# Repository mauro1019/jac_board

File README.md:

# jac_board
 Ambulance Light Controller

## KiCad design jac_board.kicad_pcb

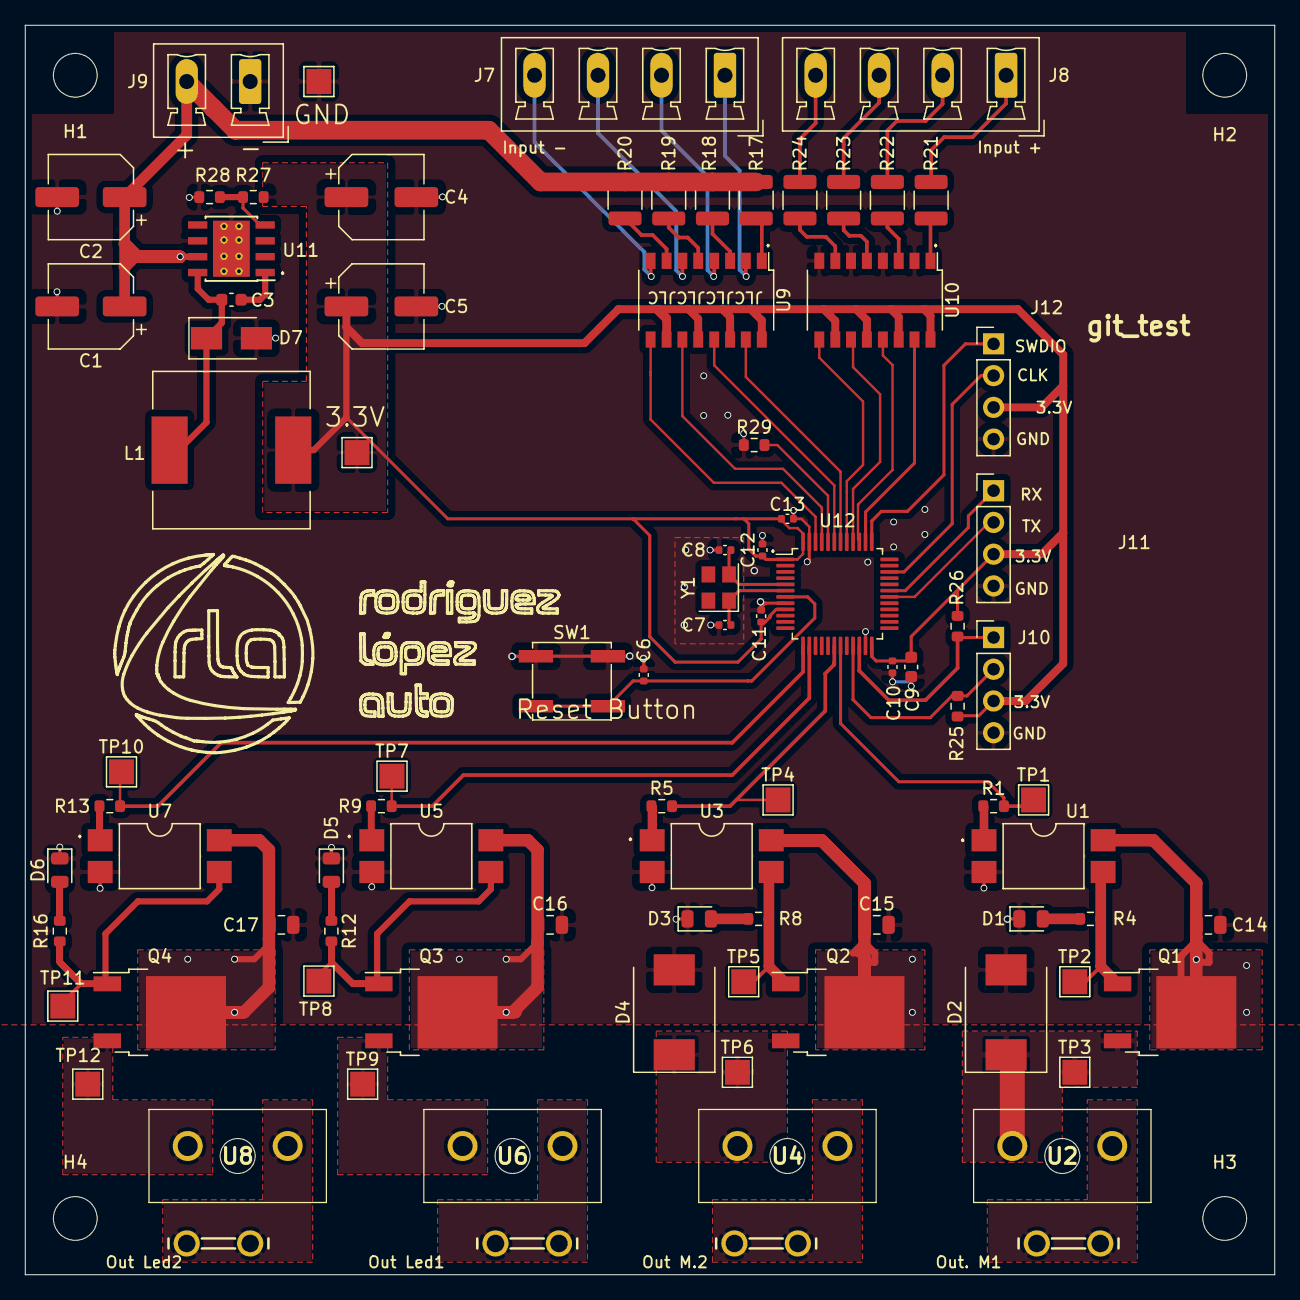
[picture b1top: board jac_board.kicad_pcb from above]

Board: 2 copper layers, 100.0 x 100.0 mm, 92 parts (0 on the bottom side), 64 nets.

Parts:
C1, C2: 22uF; CP_Elec_6.3x7.7
C3: 10nf; C_0603_1608Metric
C4, C5: 150uF; CP_Elec_6.3x5.4
C6, C10, C11, C12, C13: 100nf; C_0402_1005Metric
C7, C8: 16pf; C_0402_1005Metric
C9: 4.7uf; C_0603_1608Metric
C14, C15, C16, C17: 22uf; C_0805_2012Metric
D1, D3, D5, D6: LED; LED_0805_2012Metric
D2, D4: FlyBack Diode; D_SMC
D7: B340; D_SMA
H1, H2, H3, H4: MountingHole; MountingHole_3.5mm
J2, J3, J4, J5: 726386-2
J7, J8: Screw_Terminal_01x04; PhoenixContact_MCV_1,5_4-G-5.08_1x04_P5.08mm_Vertical
J9: Screw_Terminal_01x02; PhoenixContact_MCV_1,5_2-G-5.08_1x02_P5.08mm_Vertical
J10, J11, J12: Conn_01x04_Female; PinHeader_1x04_P2.54mm_Vertical
L1: 22uH; L_12x12mm_H6mm
Q1, Q2, Q3, Q4: KIA50N06BD; TO-252-2
R1, R5, R9, R13: 220; R_0603_1608Metric
R4, R8, R12, R16: 1k; R_0603_1608Metric
R17, R18, R19, R20, R21, R22, R23, R24: 510; R_1210_3225Metric
R25, R26: 4.7k; R_0603_1608Metric
R27, R28: 510; R_0603_1608Metric
R29: 100k; R_0603_1608Metric
SW1: SW_Push; SW_SPST_EVPBF
TP1, TP2, TP3, TP4, TP5, TP6, TP7, TP8, TP9, TP10, TP11, TP12, TP13, TP14: TestPoint; TestPoint_Pad_2.0x2.0mm
U1, U3, U5, U7: LTV-817S; SMDIP-4_W9.53mm
U2, U4, U6, U8: 178.6764.0001; 17867640001
U9, U10: LTV-247; SOP-16_4.4x10.4mm_P1.27mm
U11: TPS5430DDA; TI_SO-PowerPAD-8_ThermalVias
U12: STM32F030C8Tx; LQFP-48_7x7mm_P0.5mm
Y1: 8MHz; Oscillator_SMD_Abracon_ASE-4Pin_3.2x2.5mm

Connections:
+3V3: C4.1, C5.1, C9.1, C10.1, C11.1, C12.1, C13.1, J10.3, J11.3, J12.3, L1.2, R25.2, R26.2, R27.1, TP14.1, U9.10, U9.12, U9.14, U9.16, U10.10, U10.12, U10.14, U10.16, U12.1, U12.9, U12.24, U12.48
+12V: C1.1, C2.1, C14.1, C15.1, C16.1, C17.1, J9.2, Q1.2, Q2.2, Q3.2, Q4.2, R17.2, R18.2, R19.2, R20.2, U1.4, U3.4, U5.4, U7.4, U11.7
/optoMosfet/Sheet60DFA9C4/out_motor: D2.1, Q1.3, TP3.1, U2.1
/optoMosfet/sheet60E0E1BC/out_motor: D4.1, Q2.3, TP6.1, U4.1
GND: C1.2, C2.2, C4.2, C5.2, C6.1, C7.2, C8.2, C9.2, C10.2, C11.2, C12.2, C13.2, C14.2, C15.2, C16.2, C17.2, D1.1, D2.2, D3.1, D4.2, D5.1, D6.1, D7.2, J9.1, J10.4, J11.4, J12.4, R28.2, R29.1, SW1.1, TP13.1, U1.2, U3.2, U5.2, U7.2, U10.2, U10.4, U10.6, U10.8, U11.6, U11.9, U12.8, U12.23, U12.47
unnamed: C3.1, U11.1
unnamed: C3.2, D7.1, L1.1, U11.8
unnamed: D1.2, R4.1
unnamed: D3.2, R8.1
unnamed: D5.2, R12.1
unnamed: D6.2, R16.1
unnamed: J2.1, J2.2, U2.2
unnamed: J3.1, J3.2, U4.2
unnamed: J4.1, J4.2, U6.2
unnamed: J5.1, J5.2, U8.2
unnamed: Q1.1, R4.2, TP2.1, U1.3
unnamed: Q2.1, R8.2, TP5.1, U3.3
unnamed: Q3.1, R12.2, TP8.1, U5.3
unnamed: Q3.3, TP9.1, U6.1
unnamed: Q4.1, R16.2, TP11.1, U7.3
unnamed: Q4.3, TP12.1, U8.1
unnamed: R1.1, U1.1
unnamed: R5.1, U3.1
unnamed: R9.1, U5.1
unnamed: R13.1, U7.1
unnamed: R17.1, U9.1
unnamed: R18.1, U9.3
unnamed: R19.1, U9.5
unnamed: R20.1, U9.7
unnamed: R21.1, U10.1
unnamed: R22.1, U10.3
unnamed: R23.1, U10.5
unnamed: R24.1, U10.7
unnamed: R29.2, U12.44
PA3: R13.2, TP10.1, U12.13
PA4: R9.2, TP7.1, U12.14
PA13: J12.2, U12.34
PA14: J12.1, U12.37
PA15: U10.15, U12.38
PB0: R5.2, TP4.1, U12.18
PB1: R1.2, TP1.1, U12.19
PB3: U10.13, U12.39
PB4: U10.11, U12.40
PB5: U10.9, U12.41
PB6: U9.15, U12.42
PB7: U9.13, U12.43
PB8: U9.11, U12.45
PB9: U9.9, U12.46
RX1: J11.1, U12.31
TX1: J11.2, U12.30
i+1: J8.1, R21.2
i+2: J8.2, R22.2
i+3: J8.3, R23.2
i+4: J8.4, R24.2
i-1: J7.1, U9.2
i-2: J7.2, U9.4
i-3: J7.3, U9.6
i-4: J7.4, U9.8
rcc_osc_in: C8.1, U12.5, Y1.2
rcc_osc_out: C7.1, U12.6, Y1.1
reset: C6.2, SW1.2, U12.7
scl: J10.2, R25.1, U12.21
sda: J10.1, R26.1, U12.22
vsense: R27.2, R28.1, U11.4

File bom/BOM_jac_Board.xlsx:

Comment | Designator | Footprint | LCSC Part #（optional）
22uF | C1 | Capacitor_SMD:CP_Elec_6.3x7.7 | C134761
22uF | C2 | Capacitor_SMD:CP_Elec_6.3x7.7 | C134761
10nf | C3 | Capacitor_SMD:C_0603_1608Metric | C57112
150uF | C4 | Capacitor_SMD:CP_Elec_6.3x5.4 | C249598
150uF | C5 | Capacitor_SMD:CP_Elec_6.3x5.4 | C249598
100nf | C6 | Capacitor_SMD:C_0402_1005Metric | C15195
16pf | C7 | Capacitor_SMD:C_0402_1005Metric | C161307
16pf | C8 | Capacitor_SMD:C_0402_1005Metric | C161307
4.7uf | C9 | Capacitor_SMD:C_0603_1608Metric | C19666
100nf | C10 | Capacitor_SMD:C_0402_1005Metric | C15195
100nf | C11 | Capacitor_SMD:C_0402_1005Metric | C15195
100nf | C12 | Capacitor_SMD:C_0402_1005Metric | C15195
100nf | C13 | Capacitor_SMD:C_0402_1005Metric | C15195
22uf | C14 | Capacitor_SMD:C_0805_2012Metric | C45783
22uf | C15 | Capacitor_SMD:C_0805_2012Metric | C45783
22uf | C16 | Capacitor_SMD:C_0805_2012Metric | C45783
22uf | C17 | Capacitor_SMD:C_0805_2012Metric | C45783
LED | D1 | LED_SMD:LED_0805_2012Metric | C84256
FlyBack Diode | D2 | Diode_SMD:D_SMC | C65019
LED | D3 | LED_SMD:LED_0805_2012Metric | C84256
FlyBack Diode | D4 | Diode_SMD:D_SMC | C65019
LED | D5 | LED_SMD:LED_0805_2012Metric | C84256
LED | D6 | LED_SMD:LED_0805_2012Metric | C84256
B340 | D7 | Diode_SMD:D_SMA | C64982
MountingHole | H1 | MountingHole:MountingHole_3.5mm
MountingHole | H2 | MountingHole:MountingHole_3.5mm
MountingHole | H3 | MountingHole:MountingHole_3.5mm
MountingHole | H4 | MountingHole:MountingHole_3.5mm
726386-2 | J2 | output_terminal:726386-2 | C305817
726386-2 | J3 | output_terminal:726386-2 | C305817
726386-2 | J4 | output_terminal:726386-2 | C305817
726386-2 | J5 | output_terminal:726386-2 | C305817
Screw_Terminal_01x04 | J7 | Connector_Phoenix_MC_HighVoltage:PhoenixContact_MCV_1,5_4-G-5.08_1x04_P5.08mm_V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
Screw_Terminal_01x04 | J8 | Connector_Phoenix_MC_HighVoltage:PhoenixContact_MCV_1,5_4-G-5.08_1x04_P5.08mm_V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
Screw_Terminal_01x02 | J9 | Connector_Phoenix_MC_HighVoltage:PhoenixContact_MCV_1,5_2-G-5.08_1x02_P5.08mm_V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
Conn_01x04_Female | J10 | Connector_PinHeader_2.54mm:PinHeader_1x04_P2.54mm_Vertical
Conn_01x04_Female | J11 | Connector_PinHeader_2.54mm:PinHeader_1x04_P2.54mm_Vertical
Conn_01x04_Female | J12 | Connector_PinHeader_2.54mm:PinHeader_1x04_P2.54mm_Vertical
22uH | L1 | Inductor_SMD:L_12x12mm_H6mm | C169385
KIA50N06BD | Q1 | Package_TO_SOT_SMD:TO-252-2 | C130980
KIA50N06BD | Q2 | Package_TO_SOT_SMD:TO-252-2 | C130980
KIA50N06BD | Q3 | Package_TO_SOT_SMD:TO-252-2 | C130980
KIA50N06BD | Q4 | Package_TO_SOT_SMD:TO-252-2 | C130980
220 | R1 | Resistor_SMD:R_0603_1608Metric | C22962
1k | R4 | Resistor_SMD:R_0603_1608Metric | C21190
220 | R5 | Resistor_SMD:R_0603_1608Metric | C22962
1k | R8 | Resistor_SMD:R_0603_1608Metric | C21190
220 | R9 | Resistor_SMD:R_0603_1608Metric | C22962
1k | R12 | Resistor_SMD:R_0603_1608Metric | C21190
220 | R13 | Resistor_SMD:R_0603_1608Metric | C22962
1k | R16 | Resistor_SMD:R_0603_1608Metric | C21190
510 | R17 | Resistor_SMD:R_1210_3225Metric | C105030
510 | R18 | Resistor_SMD:R_1210_3225Metric | C105030
510 | R19 | Resistor_SMD:R_1210_3225Metric | C105030
510 | R20 | Resistor_SMD:R_1210_3225Metric | C105030
510 | R21 | Resistor_SMD:R_1210_3225Metric | C105030
510 | R22 | Resistor_SMD:R_1210_3225Metric | C105030
510 | R23 | Resistor_SMD:R_1210_3225Metric | C105030
510 | R24 | Resistor_SMD:R_1210_3225Metric | C105030
4.7k | R25 | Resistor_SMD:R_0603_1608Metric | C23162
4.7k | R26 | Resistor_SMD:R_0603_1608Metric | C23162
510 | R27 | Resistor_SMD:R_0603_1608Metric | C105030
510 | R28 | Resistor_SMD:R_0603_1608Metric | C105030
100k | R29 | Resistor_SMD:R_0603_1608Metric | C25803
SW_Push | SW1 | Button_Switch_SMD:SW_SPST_EVPBF | C318884
TestPoint | TP1 | TestPoint:TestPoint_Pad_2.0x2.0mm
TestPoint | TP2 | TestPoint:TestPoint_Pad_2.0x2.0mm
TestPoint | TP3 | TestPoint:TestPoint_Pad_2.0x2.0mm
TestPoint | TP4 | TestPoint:TestPoint_Pad_2.0x2.0mm
TestPoint | TP5 | TestPoint:TestPoint_Pad_2.0x2.0mm
TestPoint | TP6 | TestPoint:TestPoint_Pad_2.0x2.0mm
TestPoint | TP7 | TestPoint:TestPoint_Pad_2.0x2.0mm
TestPoint | TP8 | TestPoint:TestPoint_Pad_2.0x2.0mm
TestPoint | TP9 | TestPoint:TestPoint_Pad_2.0x2.0mm
TestPoint | TP10 | TestPoint:TestPoint_Pad_2.0x2.0mm
TestPoint | TP11 | TestPoint:TestPoint_Pad_2.0x2.0mm
TestPoint | TP12 | TestPoint:TestPoint_Pad_2.0x2.0mm
TestPoint | TP13 | TestPoint:TestPoint_Pad_2.0x2.0mm
TestPoint | TP14 | TestPoint:TestPoint_Pad_2.0x2.0mm
LTV-817S | U1 | Package_DIP:SMDIP-4_W9.53mm | C109226
17867640001 | U2 | fuse_holder:17867640001 | C142933
LTV-817S | U3 | Package_DIP:SMDIP-4_W9.53mm | C109226
17867640001 | U4 | fuse_holder:17867640001 | C142933
LTV-817S | U5 | Package_DIP:SMDIP-4_W9.53mm | C109226
17867640001 | U6 | fuse_holder:17867640001 | C142933
LTV-817S | U7 | Package_DIP:SMDIP-4_W9.53mm | C109226
17867640001 | U8 | fuse_holder:17867640001 | C142933
LTV-247 | U9 | Package_SO:SOP-16_4.4x10.4mm_P1.27mm | C115451
LTV-247 | U10 | Package_SO:SOP-16_4.4x10.4mm_P1.27mm | C115451
TPS5430DDA | U11 | Package_SO:TI_SO-PowerPAD-8_ThermalVias | C9864
STM32F030C8Tx | U12 | Package_QFP:LQFP-48_7x7mm_P0.5mm | C23922
8MHz | Y1 | Oscillator:Oscillator_SMD_Abracon_ASE-4Pin_3.2x2.5mm | C403948

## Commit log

2023-04-29 Primer commit - Migracion de Kicad6 a Kicad7
2023-04-29 Planteamiento nuevo proeycto de mosquito - Se eelmiraon del esquematico las entradas a 0V y las salidas a Leds
